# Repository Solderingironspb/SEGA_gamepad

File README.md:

# SEGA_gamepad
## Подключаем геймпад от SEGA Mega Drive 2 к STM32F103C8T6

##### P.S. Для новичков в программировании - готовые прошивки 100% заведутся на МК STM32F103C8T6, STM32F103CBT6, GD32F103CBT6, CH32F103C8T6. Протестировано лично. Воспользуйтесь программой STM32 ST-Link Utility. Подключитесь программатором к плате. Очистите МК. Откройте файл прошивки из папки с готовыми прошивками, например "SEGA Controller 1.bin" и залейте ее на МК. Target -> Program & Verify Ctrl + P -> Start.

**[[Смотреть видео]](https://youtu.be/_236TtiKs34)**
**[[Главная страница]](https://github.com/Solderingironspb/Lessons-Stm32/blob/master/README.md)**

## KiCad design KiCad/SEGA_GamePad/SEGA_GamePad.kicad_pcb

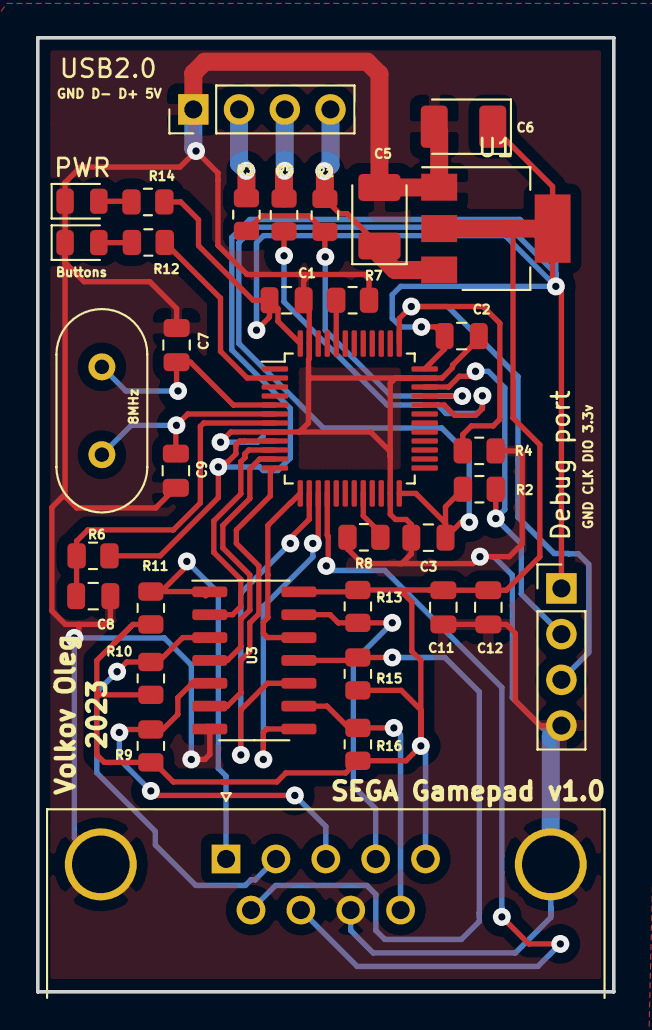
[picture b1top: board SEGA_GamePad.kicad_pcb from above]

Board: 2 copper layers, 32.0 x 53.0 mm, 36 parts (1 on the bottom side), 30 nets.

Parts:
8MHz: 8MHz; Crystal_HC49-U_Vertical
Buttons: LED; LED_0805_2012Metric
C1, C2, C3, C4, C8, C11: 0.1uF; C_0805_2012Metric
C5, C6: 47uF; CP_EIA-3528-21_Kemet-B_Pad1.50x2.35mm_HandSolder
C7, C9: 30pF; C_0805_2012Metric
C12: 10uF; C_0805_2012Metric
Debug port: Serial wire; PinHeader_1x04_P2.54mm_Vertical
PWR: LED; LED_0805_2012Metric
R1, R2, R4, R6, R7, R8: 10k; R_0805_2012Metric
R3, R5: 20; R_0805_2012Metric
R9, R10, R11, R13, R15, R16: 100k; R_0805_2012Metric
R12, R14: 1k; R_0805_2012Metric
SEGA Gamepad v1.0: SEGA; DSUB-9_Male_Horizontal_P2.77x2.84mm_EdgePinOffset4.94mm_Hou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
STM32F103: STM32F103C8Tx; LQFP-48_7x7mm_P0.5mm
U1: AMS1117-3.3; SOT-223-3_TabPin2
U3: 74HC14; SOIC-14_3.9x8.7mm_P1.27mm
USB2.0: Serial wire; PinHeader_1x04_P2.54mm_Vertical

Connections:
3.3V: C1.1, C2.1, C3.1, C4.1, C6.1, C11.1, C12.1, Debug port.1, R2.2, R6.2, R9.1, R10.1, R11.1, R13.2, R14.1, R15.2, R16.2, SEGA Gamepad v1.0.5, STM32F103.9, STM32F103.24, STM32F103.36, STM32F103.48, U1.2, U3.14
5V: C5.1, R1.2, U1.3, USB2.0.4
BOOT0: R7.2, STM32F103.44
BOOT1: R8.2, STM32F103.20
GND: Buttons.1, C1.2, C2.2, C3.2, C4.2, C5.2, C6.2, C7.1, C8.2, C9.1, C11.2, C12.2, Debug port.4, PWR.1, R4.1, R7.1, R8.1, SEGA Gamepad v1.0.0, SEGA Gamepad v1.0.8, STM32F103.8, STM32F103.23, STM32F103.35, STM32F103.47, U1.1, U3.7, USB2.0.1
LED: R12.1, STM32F103.2
NRST: C8.1, R6.1, STM32F103.7
unnamed: Buttons.2, R12.2
unnamed: PWR.2, R14.2
unnamed: R5.2, USB2.0.3
unnamed: R3.2, USB2.0.2
unnamed: R11.2, SEGA Gamepad v1.0.1, U3.1
unnamed: R10.2, SEGA Gamepad v1.0.2, U3.3
unnamed: R9.2, SEGA Gamepad v1.0.3, U3.5
unnamed: R13.1, SEGA Gamepad v1.0.4, U3.13
unnamed: R15.1, SEGA Gamepad v1.0.6, U3.11
unnamed: R16.1, SEGA Gamepad v1.0.9, U3.9
PA0: STM32F103.10, U3.2
PA1: STM32F103.11, U3.4
PA2: STM32F103.12, U3.6
PA3: STM32F103.13, U3.12
PA4: STM32F103.14, U3.10
PA5: STM32F103.15, U3.8
PA6: SEGA Gamepad v1.0.7, STM32F103.16
PA11: R5.1, STM32F103.32
PA12: R1.1, R3.1, STM32F103.33
PA13: Debug port.2, R2.1, STM32F103.34
PA14: Debug port.3, R4.2, STM32F103.37
PD0: 8MHz.1, C7.2, STM32F103.5
PD1: 8MHz.2, C9.2, STM32F103.6

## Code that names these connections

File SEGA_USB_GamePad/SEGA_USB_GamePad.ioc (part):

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Mcu.Name=STM32F103C(8-B)Tx
Mcu.Package=LQFP48
Mcu.UserName=STM32F103C8Tx
PA11.Mode=Device
PA11.Signal=USB_DM
PA12.Mode=Device
PA12.Signal=USB_DP
PA13.Mode=Serial_Wire
PA13.Signal=SYS_JTMS-SWDIO
PA14.Mode=Serial_Wire
PA14.Signal=SYS_JTCK-SWCLK
PD0-OSC_IN.Mode=HSE-External-Oscillator
PD0-OSC_IN.Signal=RCC_OSC_IN
PD1-OSC_OUT.Mode=HSE-External-Oscillator
PD1-OSC_OUT.Signal=RCC_OSC_OUT
RCC.SYSCLKFreq_VALUE=72000000
RCC.SYSCLKSource=RCC_SYSCLKSOURCE_PLLCLK
board=custom

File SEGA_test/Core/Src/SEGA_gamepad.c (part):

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void SEGA_GPIO_Init(void){
    /*Настройка ножек*/
    SET_BIT(RCC->APB2ENR, RCC_APB2ENR_IOPAEN); //Запуск тактирования порта А
    //PA0 - PIN1(Input floating)
    MODIFY_REG(GPIOA->CRL, GPIO_CRL_MODE0_Msk, 0b00 << GPIO_CRL_MODE0_Pos);
    MODIFY_REG(GPIOA->CRL, GPIO_CRL_CNF0_Msk, 0b01 << GPIO_CRL_CNF0_Pos);
    //PA1 - PIN2(Input floating)
    MODIFY_REG(GPIOA->CRL, GPIO_CRL_MODE1_Msk, 0b00 << GPIO_CRL_MODE1_Pos);
    MODIFY_REG(GPIOA->CRL, GPIO_CRL_CNF1_Msk, 0b01 << GPIO_CRL_CNF1_Pos);
    //PA2 - PIN3(Input floating)
    MODIFY_REG(GPIOA->CRL, GPIO_CRL_MODE2_Msk, 0b00 << GPIO_CRL_MODE2_Pos);
    MODIFY_REG(GPIOA->CRL, GPIO_CRL_CNF2_Msk, 0b01 << GPIO_CRL_CNF2_Pos);
    //PA3 - PIN4(Input floating)
    MODIFY_REG(GPIOA->CRL, GPIO_CRL_MODE3_Msk, 0b00 << GPIO_CRL_MODE3_Pos);
    MODIFY_REG(GPIOA->CRL, GPIO_CRL_CNF3_Msk, 0b01 << GPIO_CRL_CNF3_Pos);
    //PA4 - PIN6(Input floating)
    MODIFY_REG(GPIOA->CRL, GPIO_CRL_MODE4_Msk, 0b00 << GPIO_CRL_MODE4_Pos);
    MODIFY_REG(GPIOA->CRL, GPIO_CRL_CNF4_Msk, 0b01 << GPIO_CRL_CNF4_Pos);
    //PA5 - PIN9(Input floating)
    MODIFY_REG(GPIOA->CRL, GPIO_CRL_MODE5_Msk, 0b00 << GPIO_CRL_MODE5_Pos);
    MODIFY_REG(GPIOA->CRL, GPIO_CRL_CNF5_Msk, 0b01 << GPIO_CRL_CNF5_Pos);
    //A6 - PIN7 SELECT (Output push-pull)
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
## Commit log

2023-02-09 Пример подключения геймпада к STM32F103C8T6
2023-02-09 USB GamePad
2023-02-25 26.02.2023 - 3D, KiCad, code
2023-03-12 13.03.2023 - 3D, KiCad, code
2023-03-14 14.03.2023 - Добавлены готовые прошивки. Сделан релиз
